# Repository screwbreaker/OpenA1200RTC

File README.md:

# OpenA1200RTC
OpenA1200RTC is an Open Hardware RTC module for the Amiga 1200.

### Summary
This RTC circuit is actually used on other free projects like:
The [mini A501](http://eab.abime.net/showthread.php?t=85395) for Amiga 500,
The [OpenAmiga600RamExpansion](https://github.com/SukkoPera/OpenAmiga600RamExpansion) for Amiga 600.

The main goal was to made an RTC module using the same components, same clock IC, same battery holder, etc.
In this way with pratically the same BOM is possible to have the RTC for most of the Amiga computers family, A500, A600 ad now also the A1200.

#### BOM
The entire RTC circuit has been designed for an Epson [RTC62421](http://pdf.datasheetcatalog.com/datasheets/90/339927_DS.pdf) or [RTC72421](http://pdf.datasheetcatalog.com/datasheet/epson/RTC-72423.pdf), which don't need an external crystal nor any calibration. Both can be bought very cheaply from China; they will most likely be second-hand "pulls", but usually they will work fine.

The other components have some degree of flexibility:
- C1: 100 nF 0805 capacitor
- C2: >= 2.2 μF >= 10 V 1206 tantalum capacitor
- R1, R2, R3: 10K 0805 resistor
- R4, R5: 220-470 0805 resistor
- D1: BAT721C or BAT54C diode
- Battery Holder: Some cheap eBay one, usually called *BS-7*
- Battery: CR2032 3V Non-Rechargeable Lithium (a new one will last years)
- Connector: 2x20 2mm pitch straight female pin header

Note that if you plan to store your Amiga or not to use it in a while, **you are recommended to remove the battery**. Failing to do this killed many A500+ computers and many A501 expansions in the past. The CR2032 battery used in this project is probably safer than the batteries used in those devices, but still I would not leave one in an unused Amiga. You have been warned.

### Installation
Open the A1200, locate the P9B connector, it is between the Kickstart ROMs and the RAM ICs.
The PB9 is a 40 pin connector, but in most A1200 only the 22 on the right are populated. And they are the only pins needed to allow the RTC to work.
On this board a full 40 pin connector is used, mostly because it seem easier to find, and because help to avoid mistakes in the installation.

Align the pin 1 of the board with the pin 1 of the PB9 connector and gently push it down, an extra silkscreen on the PCB help to identify and align the 22 usable pins.

This board is not designed specifically to fit with the shield, but, nevertheless it seem to fit even with it. Except for the little RTC cover of the shield, that must be removed.
The board was made specifically for reuse the same components of other expansions, so the shape was made according to the size of the components, not for be an optimal fit into any A1200.
There could be space problems with other expansion. In this case I suggest to look for other RTC modules specifically made to be smaller.

If an accelerator board with the RTC module is installed, don't use this board, or disable one of the two RTC.
To disable this board open the jumper JP1.

There are also some expansions that use the clock port for other things than the RTC, I have no clue if this board will work with them, or even if it can fit on them.

### License
OpenA1200RTC is Open Hardware. If you make any modifications to the board, please contribute them back.

### Disclaimer
OpenA1200RTC is provided to you 'as is' and without any express or implied warranties whatsoever with respect to its functionality, operability or use, including, without limitation, any implied warranties of merchantability, fitness for a particular purpose or infringement. We expressly disclaim any liability whatsoever for any direct, indirect, consequential, incidental or special damages, including, without limitation, lost revenues, lost profits, losses resulting from business interruption or loss of data, regardless of the form of action or legal theory under which the liability may be asserted, even if advised of the possibility or likelihood of such damages.

### Support the Project
Since the project is open you are free to get the PCBs made by your preferred manufacturer, however in case you want to support the development, you can order them from PCBWay:

You get cheap, professionally-made and good quality PCBs, that will help with this and [other projects](https://www.pcbway.com/project/member/?bmbno=W123483A). You won't even have to worry about the various PCB options, it's all pre-configured for you!

Also, if you still have to register to that site, [you can use this link](https://www.pcbway.com/setinvite.aspx?inviteid=269036) to get some bonus initial credit (and some more to help the author of projects like this).

Again, if you want to use another manufacturer, feel free to, don't feel obligated :).

### Thanks
- Thanks to [SukkoPera](https://github.com/SukkoPera) for the help in the development.
- The RTC circuit was copied from the [OpenAmiga600RamExpansion](https://github.com/SukkoPera/OpenAmiga600RamExpansion).
- Footprint for BS-7 Battery Holder taken from the [digikey-kicad-library](https://github.com/digikey/digikey-kicad-library).

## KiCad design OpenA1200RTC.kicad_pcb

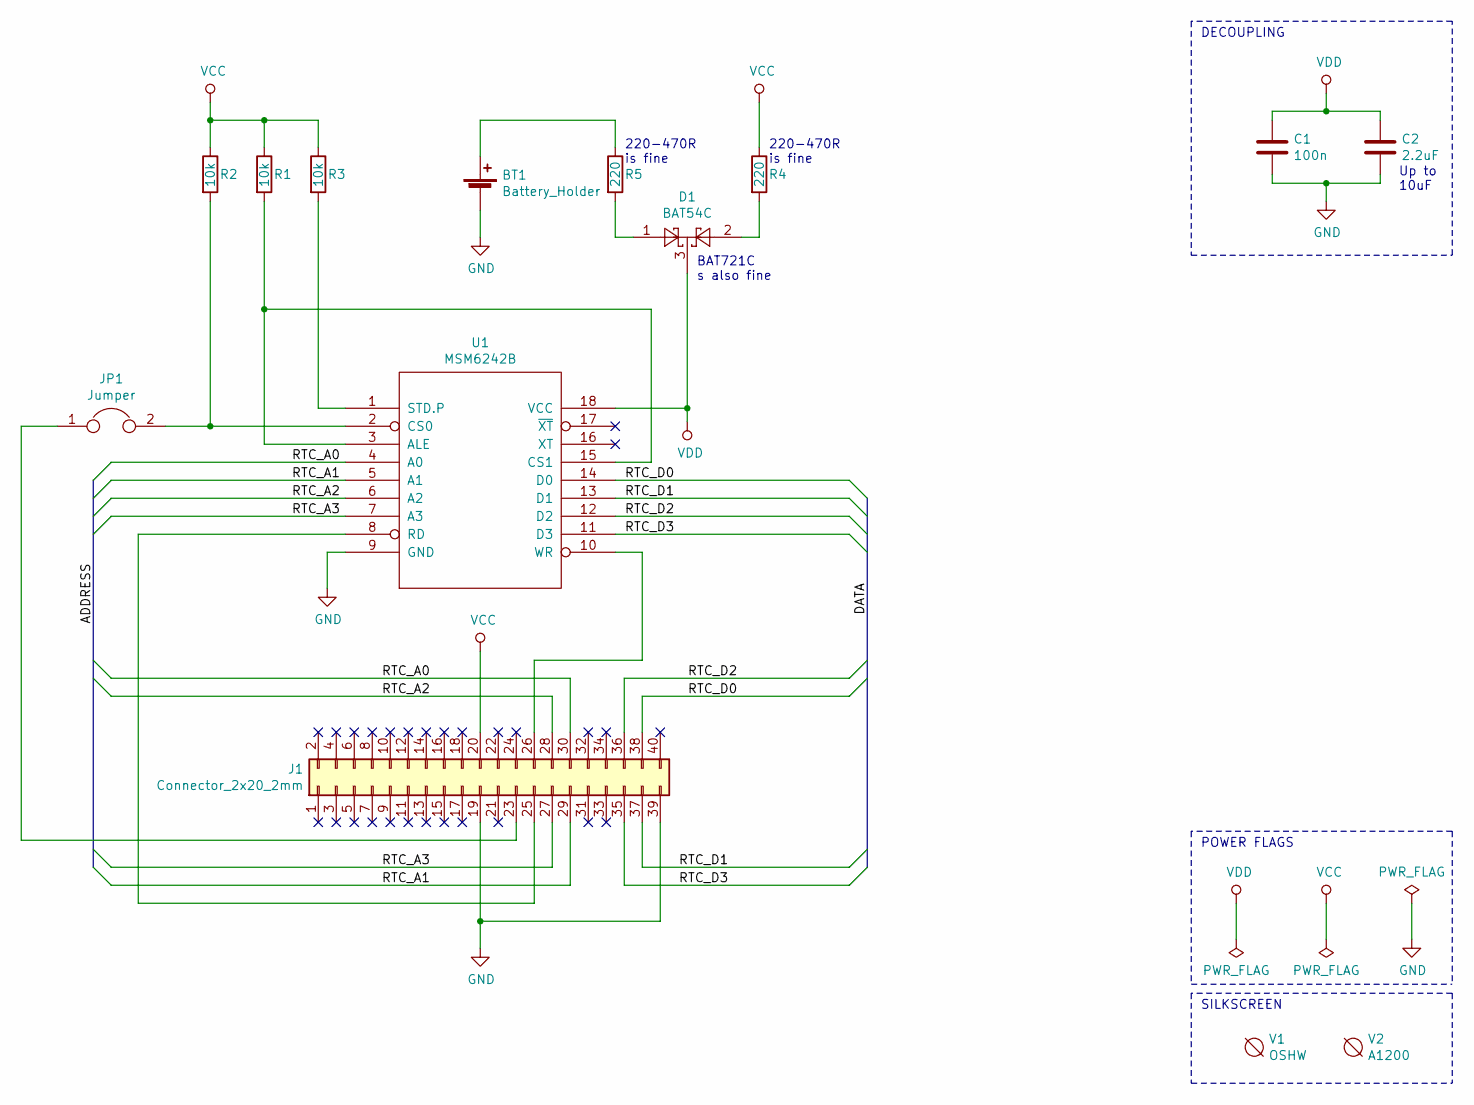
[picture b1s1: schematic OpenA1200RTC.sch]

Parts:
BT1: Battery_Holder; Battery_Holder_Coin_2032_BS-7
C1: 100n; C_0805_HandSoldering
C2: 2.2uF; C_1206_HandSoldering
D1: BAT54C; SOT-23
J1: Connector_2x20_2mm; Pin_Header_Straight_2x20_Pitch2.00mm
JP1: Jumper; Pin_Header_Straight_1x02_Pitch2.54mm
R1, R2, R3: 10k; R_0805_HandSoldering
R4, R5: 220; R_0805_HandSoldering
U1: MSM6242B; DIP-18_W7.62mm_Socket
V1: OSHW; oshw
V2: A1200

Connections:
/RTC_A0: J1.30, U1.4 (A0)
/RTC_A1: J1.29, U1.5 (A1)
/RTC_A2: J1.28, U1.6 (A2)
/RTC_A3: J1.27, U1.7 (A3)
/RTC_D0: J1.38, U1.14 (D0)
/RTC_D1: J1.37, U1.13 (D1)
/RTC_D2: J1.36, U1.12 (D2)
/RTC_D3: J1.35, U1.11 (D3)
GND: BT1.2 (-), C1.2, C2.2, J1.19, J1.39, U1.9 (GND)
unnamed: BT1.1 (+), R5.1
unnamed: D1.1, R5.2
unnamed: D1.2, R4.2
unnamed: J1.23, JP1.1
unnamed: J1.25, U1.8 (RD)
unnamed: J1.26, U1.10 (WR)
unnamed: JP1.2, R2.2, U1.2 (CS0)
unnamed: R1.2, U1.3 (ALE), U1.15 (CS1)
unnamed: R3.2, U1.1 (STD.P)
VCC: J1.20, R1.1, R2.1, R3.1, R4.1
VDD: C1.1, C2.1, D1.3, U1.18 (VCC)

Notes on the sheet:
DECOUPLING
POWER FLAGS
Up to 10uF
SILKSCREEN
220-470R is fine
BAT721C s also fine

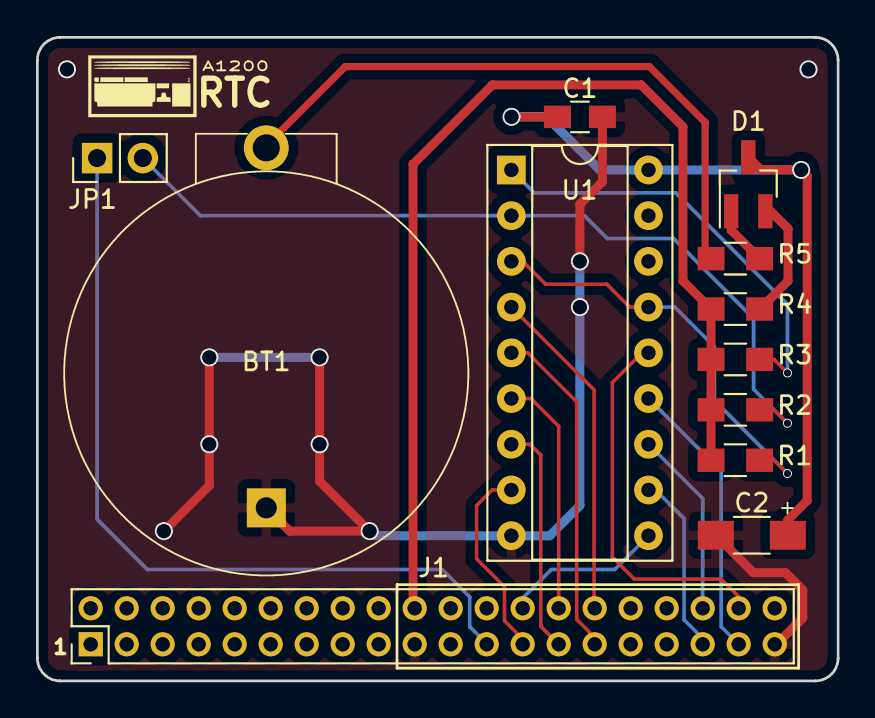
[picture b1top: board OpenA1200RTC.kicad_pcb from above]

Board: 2 copper layers, 44.5 x 35.8 mm, 14 parts (1 on the bottom side), 20 nets.

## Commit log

2019-01-29 empty file
2019-01-29 BS-7 datasheet
2019-01-29 MSM6242B datasheet
2019-01-29 render top
2019-01-29 render bottom
2019-01-29 schematic
2019-01-29 README
2019-01-29 BS-7 3D model
2019-01-29 interactive BOM
2019-01-29 BOM list
2019-01-29 gerbers
2019-01-29 A1200 symbol
2019-01-29 BS-7 battery holder
2019-01-29 OSHW logo
2019-01-29 library files
2019-01-29 local library
2019-01-29 netlist
2019-01-29 project file
2019-01-29 library
2019-02-17 old logo
2019-02-17 Handsoldering footprint for D1
2019-04-01 New README.md
